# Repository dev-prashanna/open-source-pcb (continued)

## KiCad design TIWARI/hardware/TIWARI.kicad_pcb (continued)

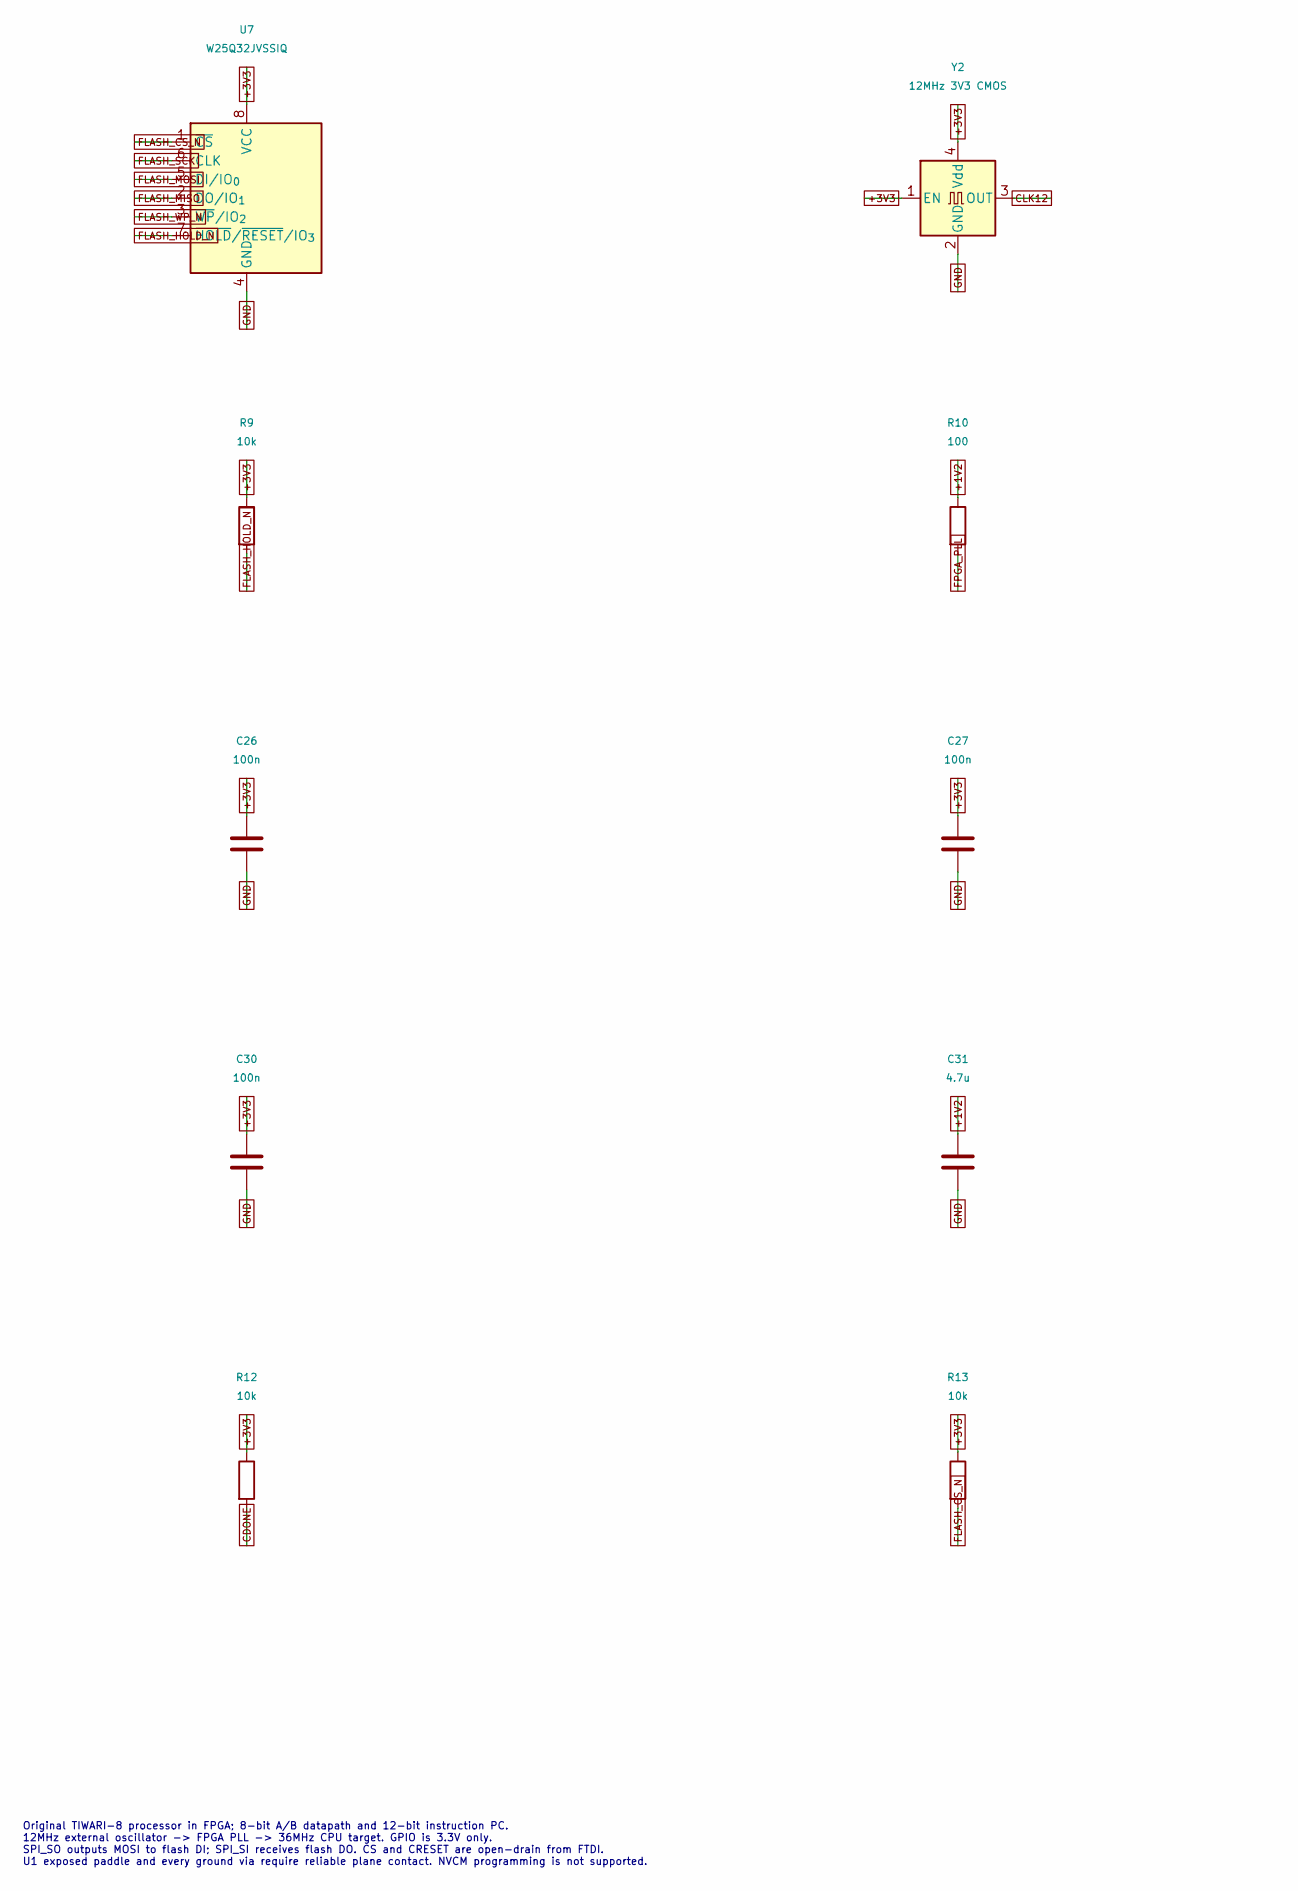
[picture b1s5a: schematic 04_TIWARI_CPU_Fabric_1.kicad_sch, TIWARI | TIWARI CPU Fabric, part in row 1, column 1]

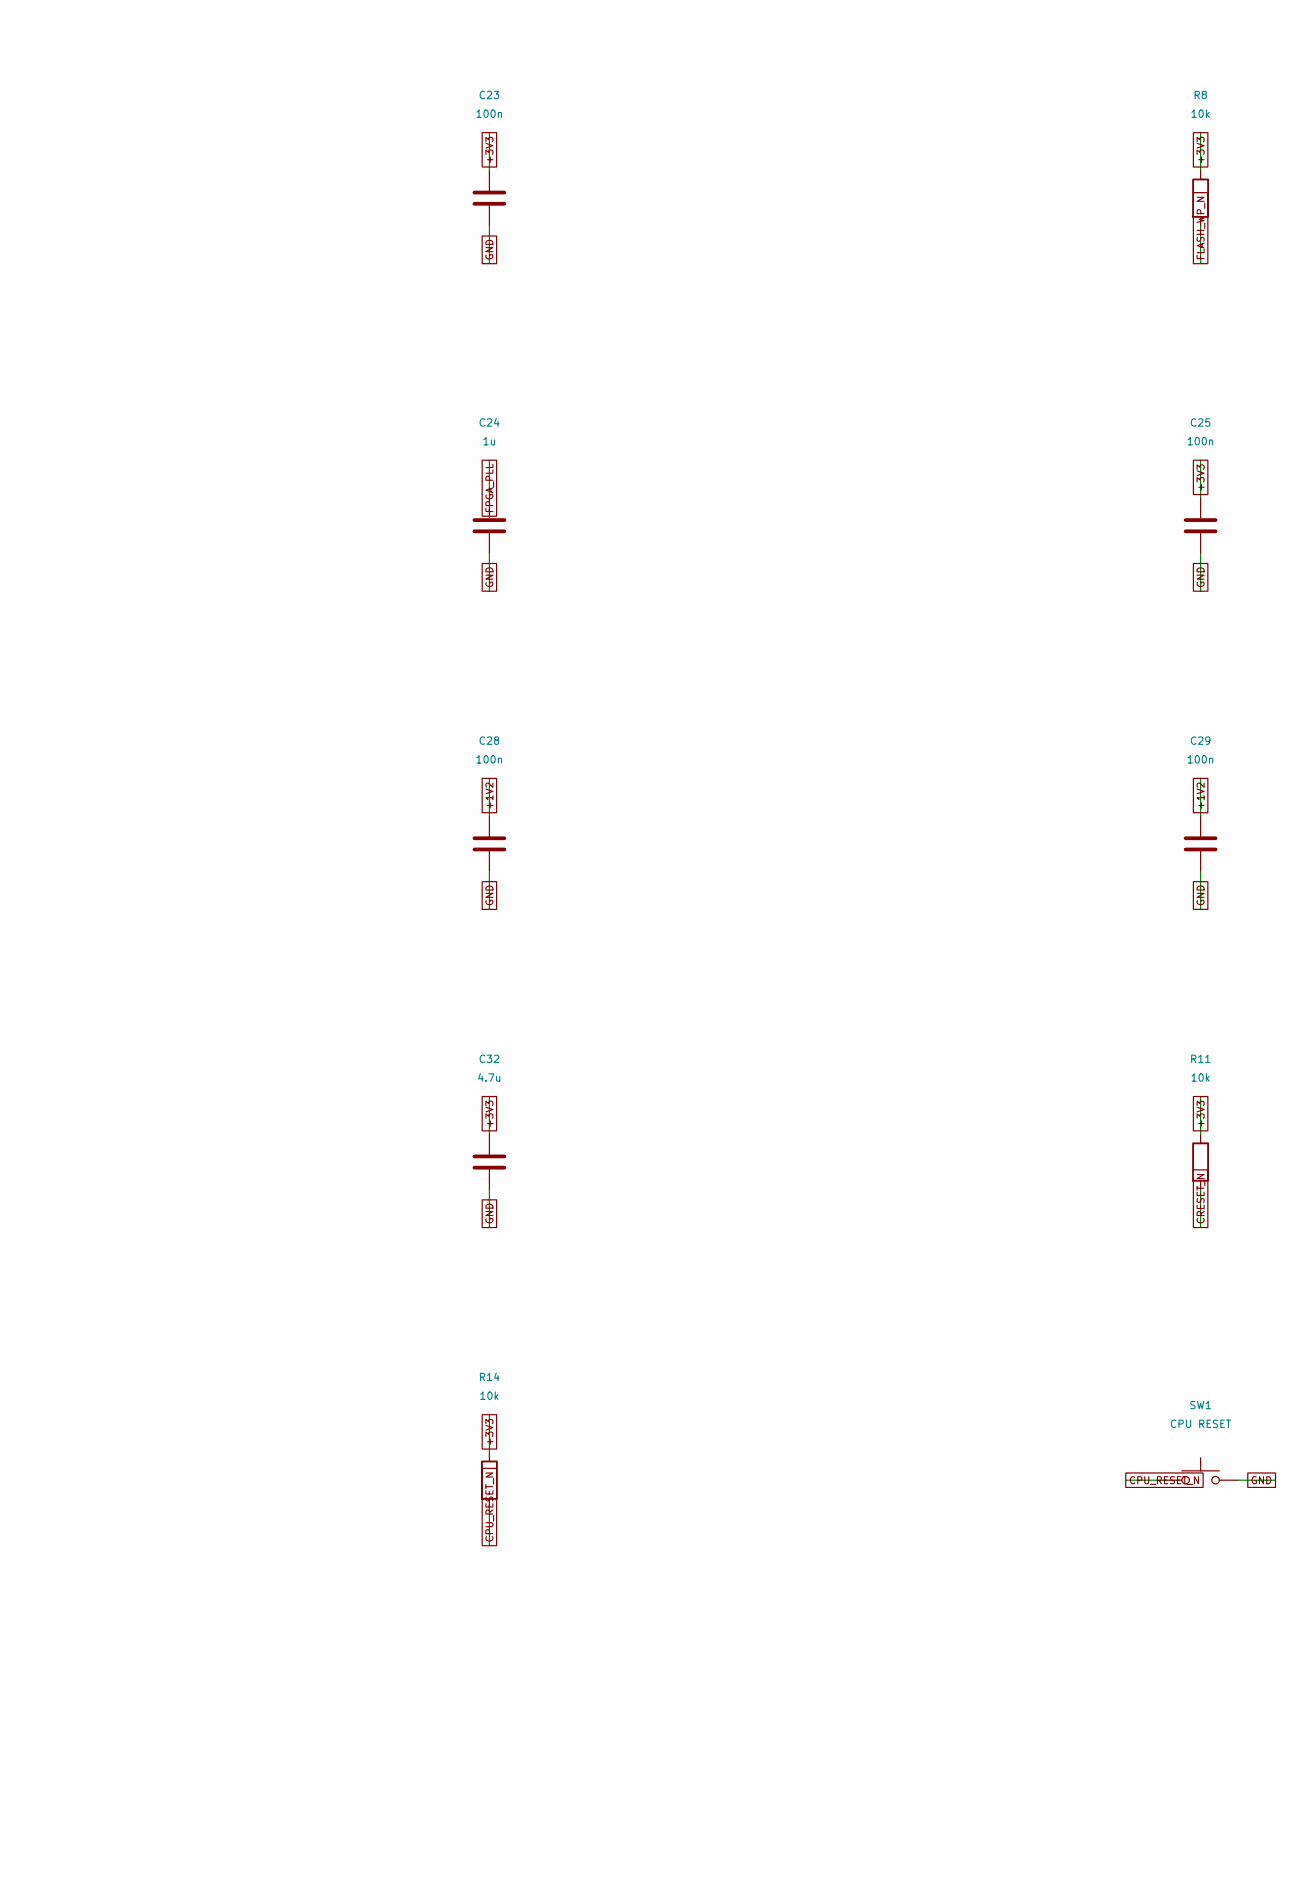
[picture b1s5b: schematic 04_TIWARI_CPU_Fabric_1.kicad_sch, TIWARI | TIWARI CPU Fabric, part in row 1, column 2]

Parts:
C23, C25, C26, C27, C28, C29, C30: 100n; C_0603_1608Metric; MPN GRM188R71C104KA01D
C24: 1u; C_0603_1608Metric; MPN GRM188R61A105KA61D
C31, C32: 4.7u; C_0805_2012Metric; MPN GRM21BR61A475KA73L
R8, R9, R11, R12, R13, R14: 10k; R_0603_1608Metric; MPN RC0603FR-0710KL
R10: 100; R_0603_1608Metric; MPN RC0603FR-07100RL
SW1: CPU RESET; SW_Push_1P1T-SH_NO_CK_KMR2xxG; MPN KMR221GLFS
U7: W25Q32JVSSIQ; SOIC-8_5.3x5.3mm_P1.27mm; MPN W25Q32JVSSIQ
Y2: 12MHz 3V3 CMOS; Oscillator_SMD_Abracon_ASE-4Pin_3.2x2.5mm; MPN ASE-12.000MHZ-LC-T

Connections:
+1V2: C28.1, C29.1, C31.1, R10.1; also elsewhere on the board
+3V3: C23.1, C25.1, C26.1, C27.1, C30.1, C32.1, R8.1, R9.1, R11.1, R12.1, R13.1, R14.1, U7.8 (VCC), Y2.1 (EN), Y2.4 (Vdd); also elsewhere on the board
CDONE: R12.2; also elsewhere on the board
CLK12: Y2.3 (OUT); also elsewhere on the board
CPU_RESET_N: R14.2, SW1.1; also elsewhere on the board
CRESET_N: R11.2; also elsewhere on the board
FLASH_CS_N: R13.2, U7.1 (~CS); also elsewhere on the board
FLASH_HOLD_N: R9.2, U7.7 (~HOLD/~RESET/IO_{3})
FLASH_MISO: U7.2 (DO/IO_{1}); also elsewhere on the board
FLASH_MOSI: U7.5 (DI/IO_{0}); also elsewhere on the board
FLASH_SCK: U7.6 (CLK); also elsewhere on the board
FLASH_WP_N: R8.2, U7.3 (~WP/IO_{2})
FPGA_PLL: C24.1, R10.2; also elsewhere on the board
GND: C23.2, C24.2, C25.2, C26.2, C27.2, C28.2, C29.2, C30.2, C31.2, C32.2, SW1.2, U7.4 (GND), Y2.2 (GND); also elsewhere on the board

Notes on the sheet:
Original TIWARI-8 processor in FPGA; 8-bit A/B datapath and 12-bit instruction PC. 12MHz external oscillator -> FPGA PLL -> 36MHz CPU target. GPIO is 3.3V only. SPI_SO outputs MOSI to flash DI; SPI_SI receives flash DO. CS and CRESET are open-drain from FTDI. U1 exposed paddle and every ground via 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

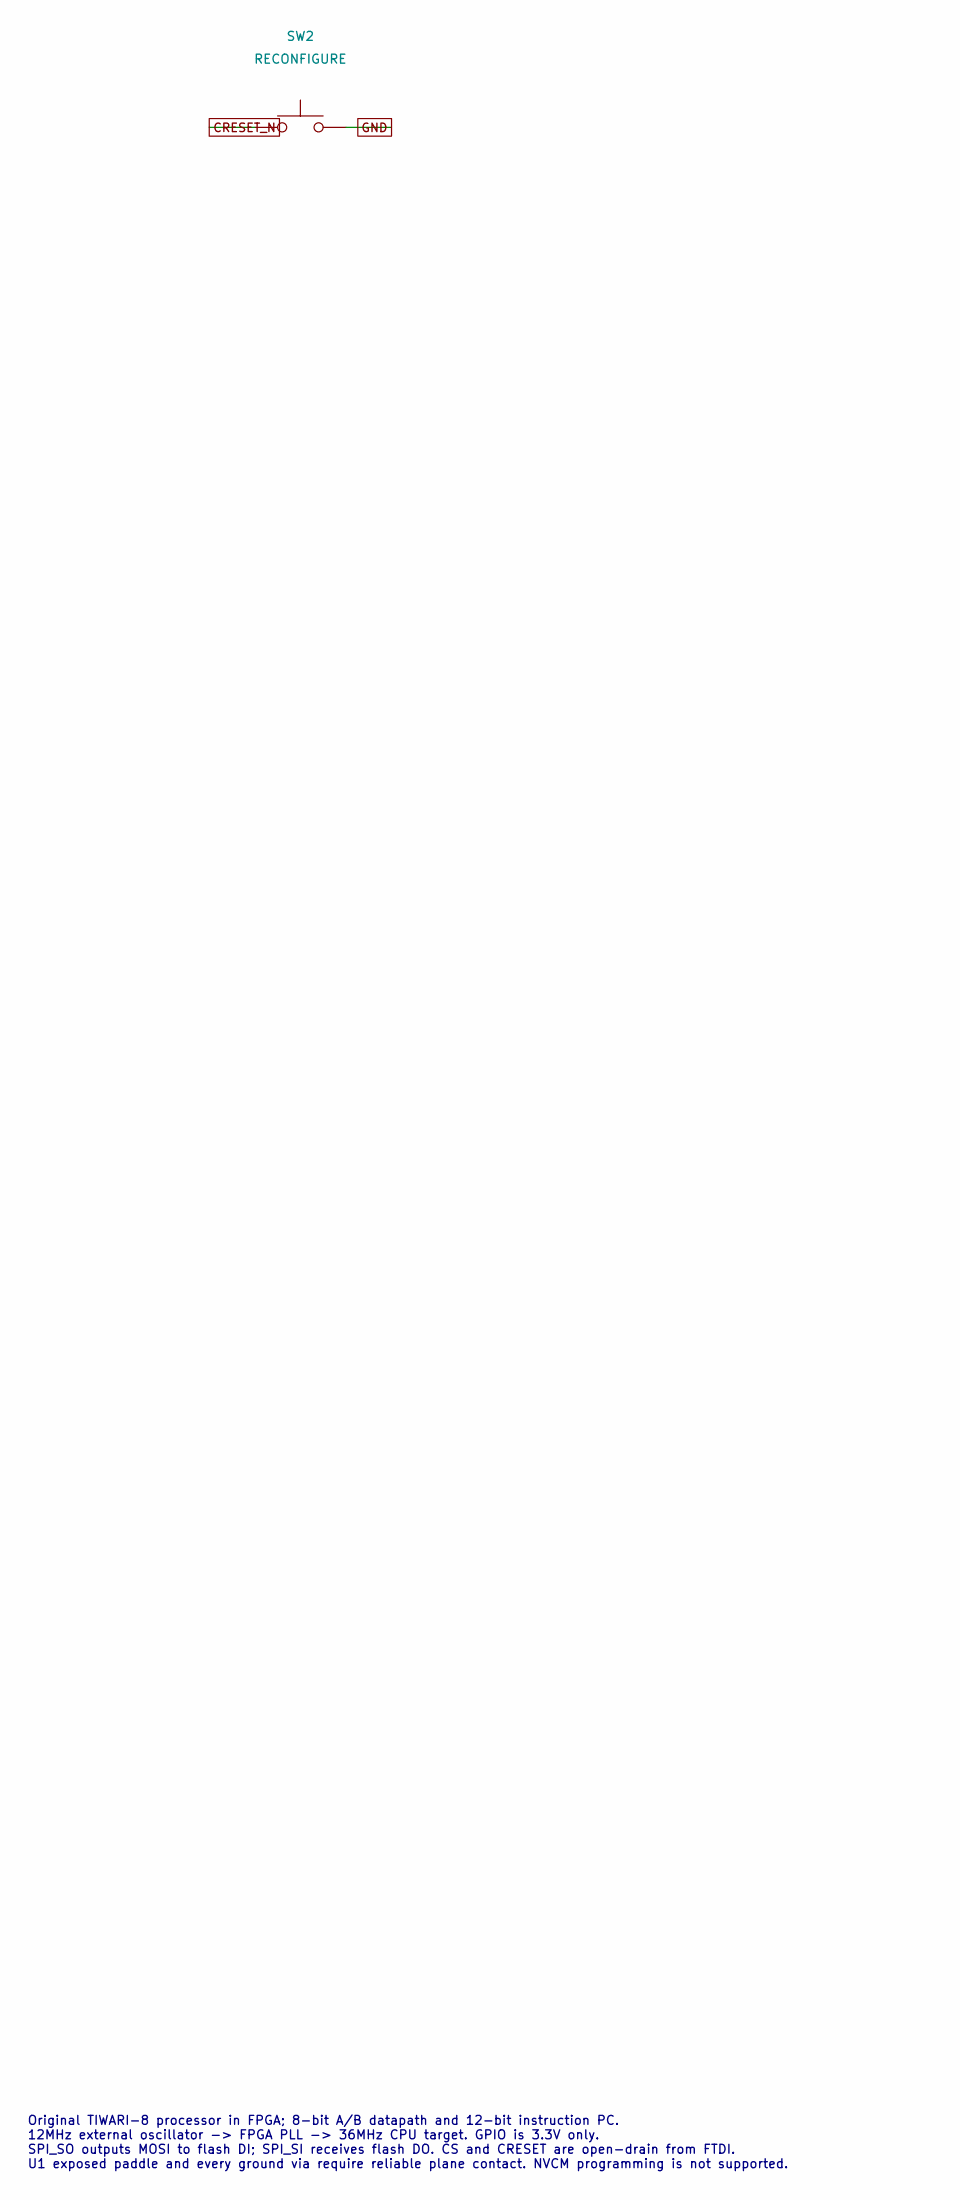
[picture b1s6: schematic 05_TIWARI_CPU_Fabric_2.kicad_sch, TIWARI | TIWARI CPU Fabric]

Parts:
SW2: RECONFIGURE; SW_Push_1P1T-SH_NO_CK_KMR2xxG; MPN KMR221GLFS

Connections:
CRESET_N: SW2.1; also elsewhere on the board
GND: SW2.2; also elsewhere on the board

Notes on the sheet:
Original TIWARI-8 processor in FPGA; 8-bit A/B datapath and 12-bit instruction PC. 12MHz external oscillator -> FPGA PLL -> 36MHz CPU target. GPIO is 3.3V only. SPI_SO outputs MOSI to flash DI; SPI_SI receives flash DO. CS and CRESET are open-drain from FTDI. U1 exposed paddle and every ground via 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

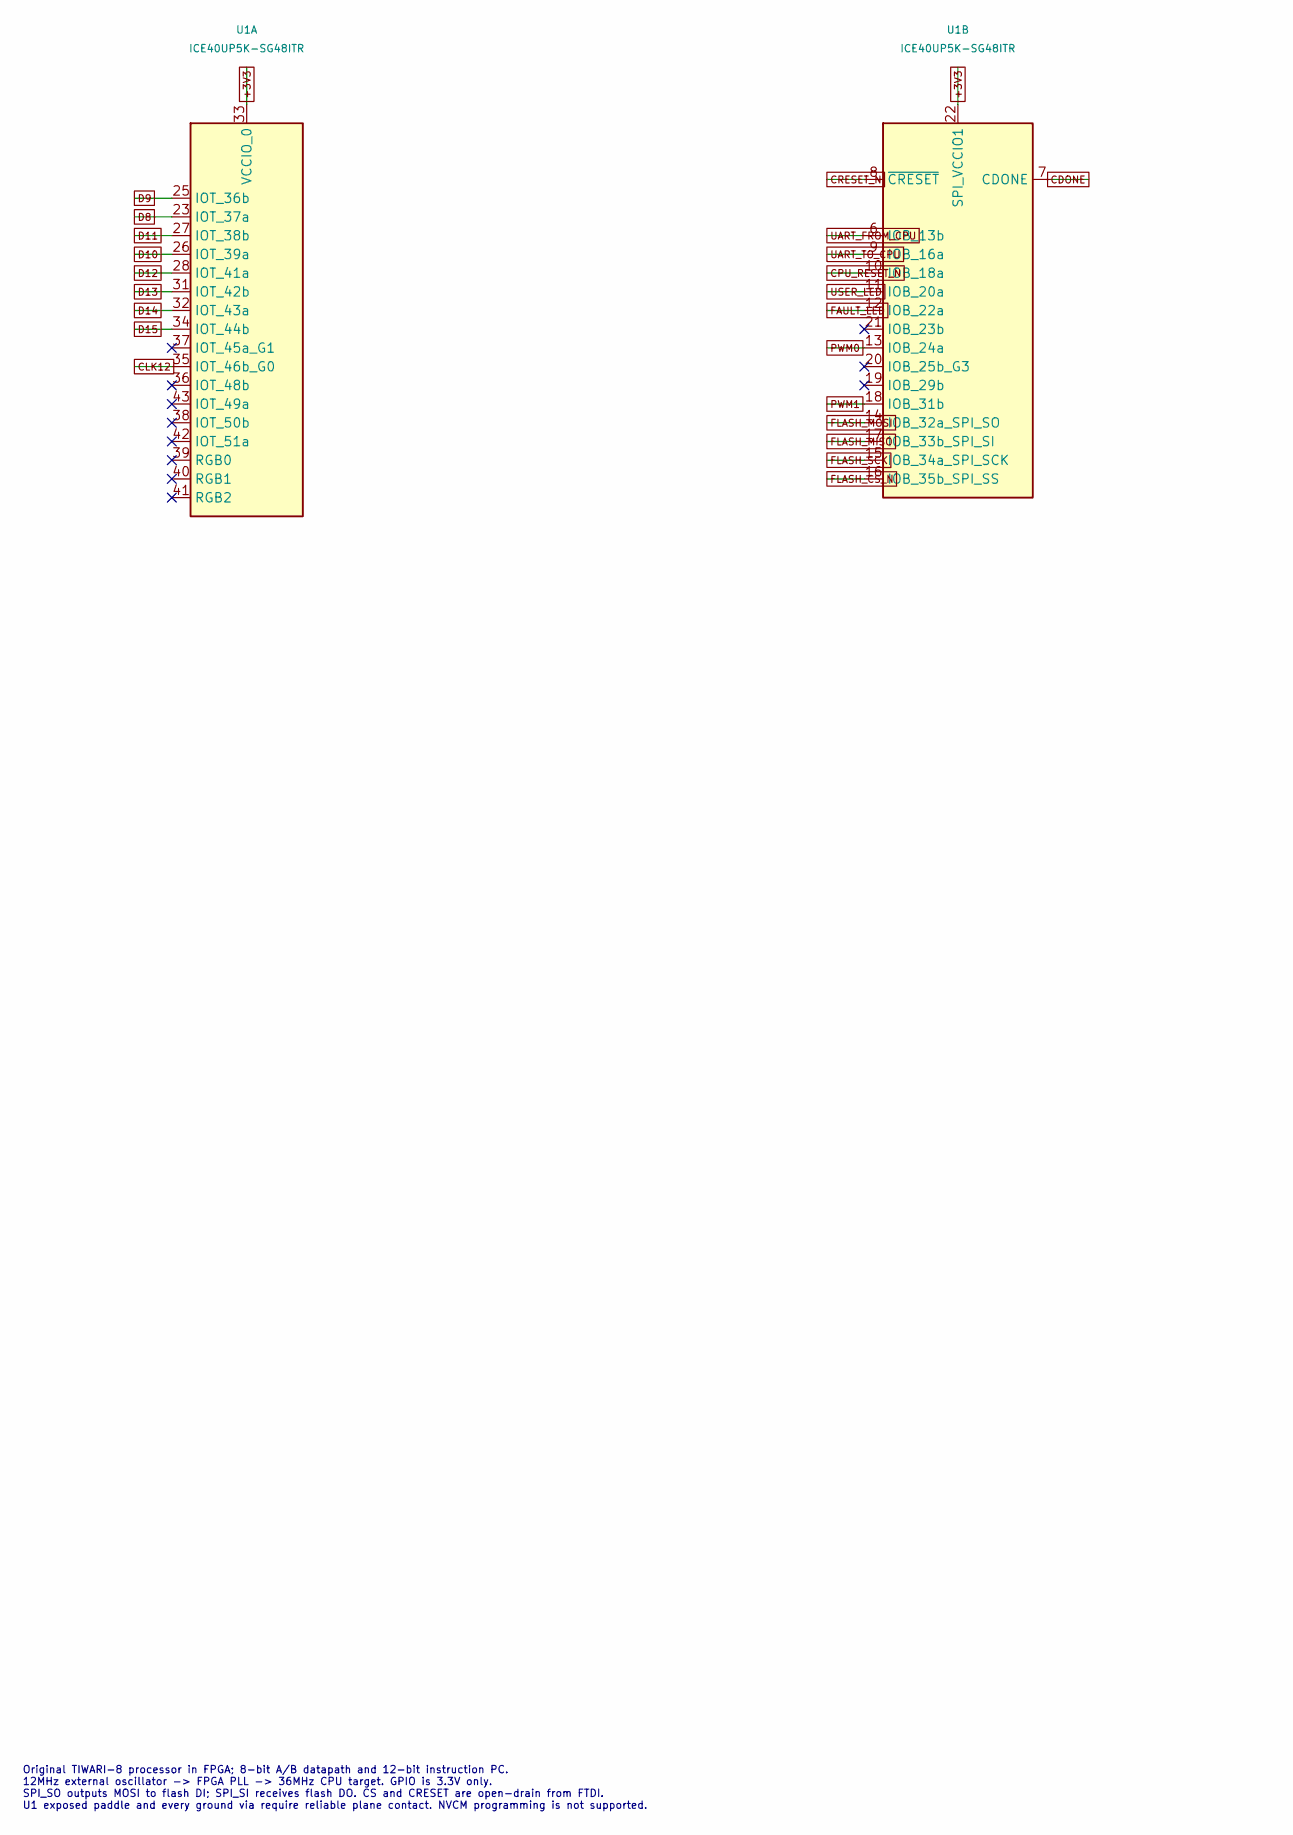
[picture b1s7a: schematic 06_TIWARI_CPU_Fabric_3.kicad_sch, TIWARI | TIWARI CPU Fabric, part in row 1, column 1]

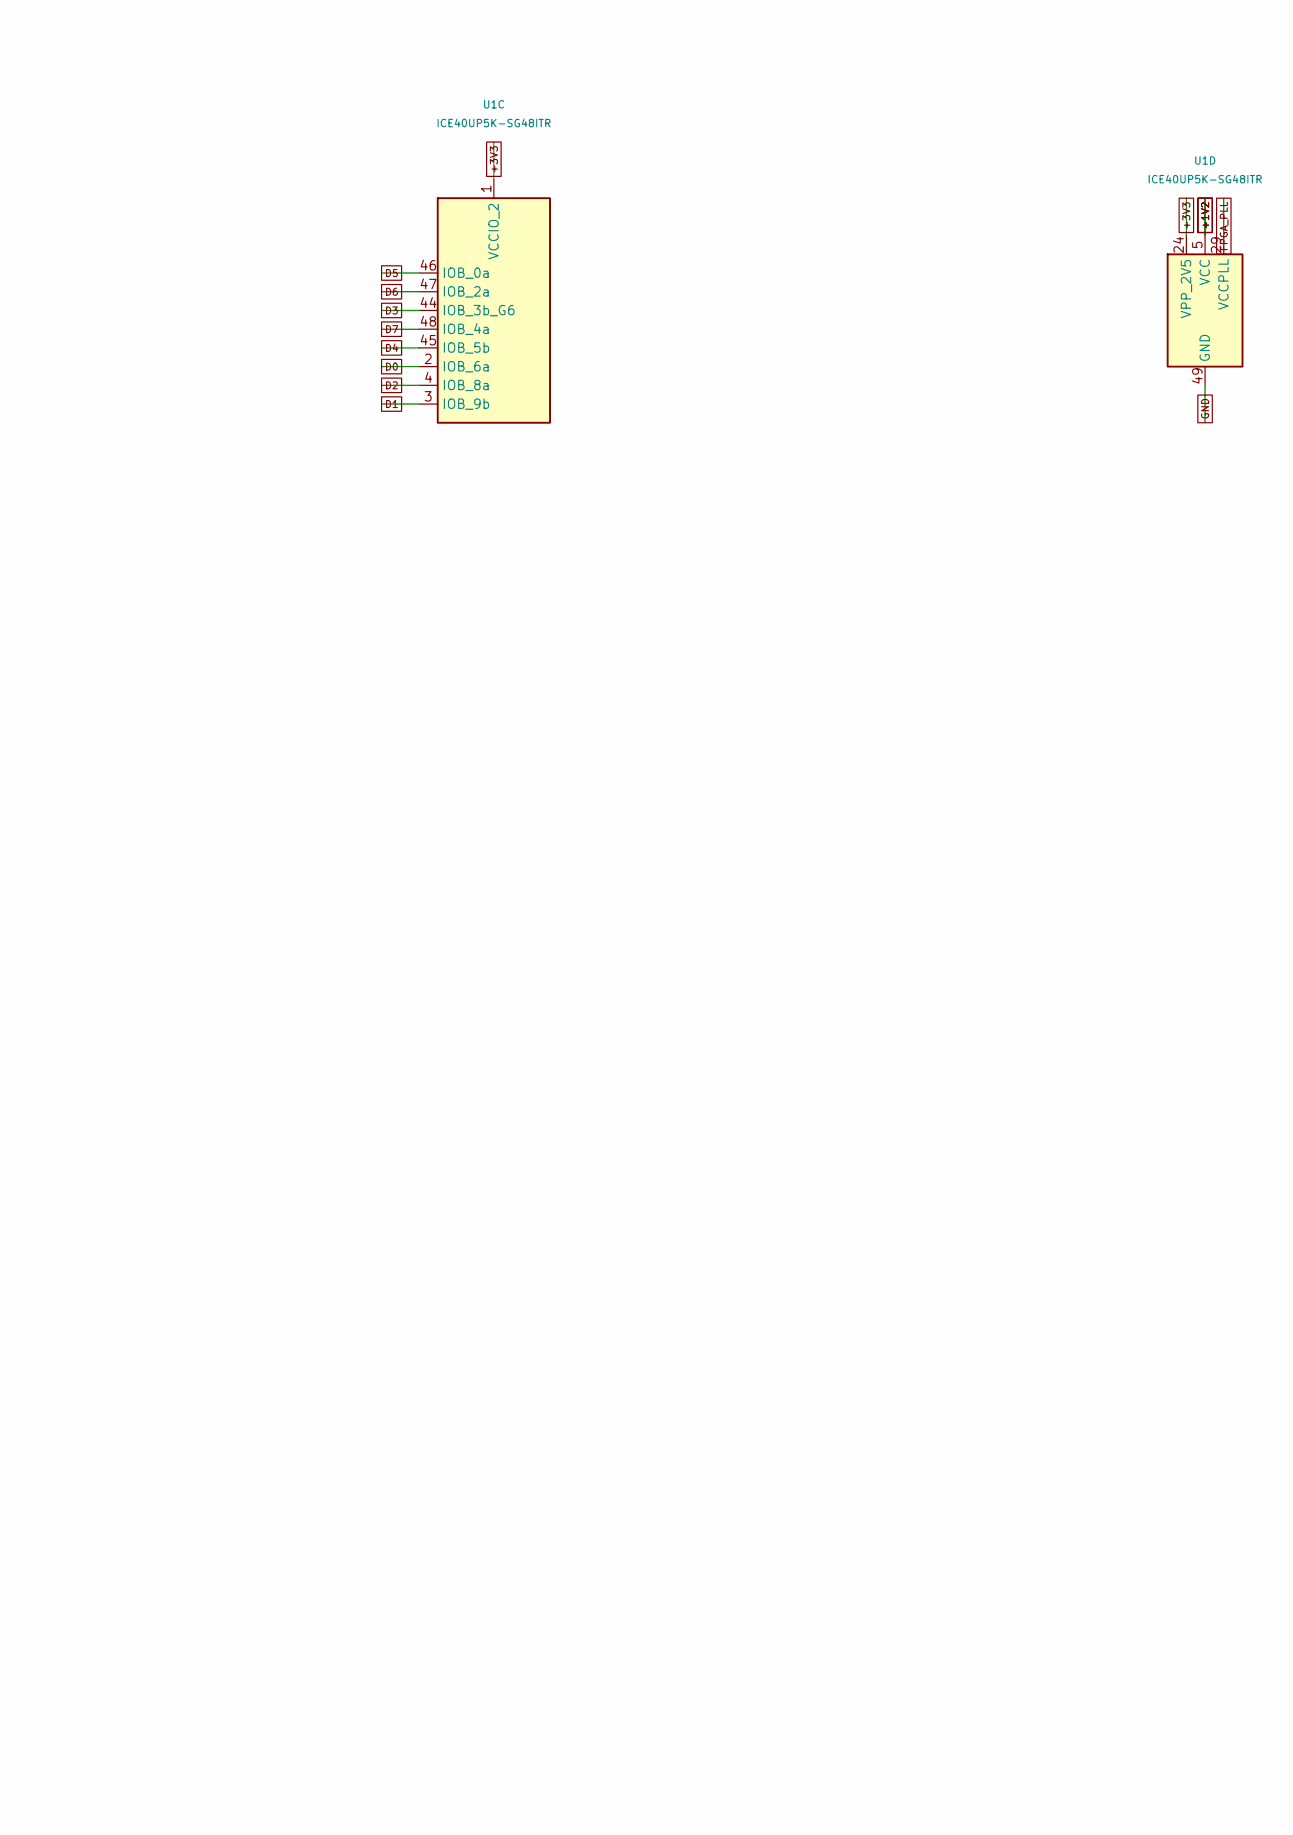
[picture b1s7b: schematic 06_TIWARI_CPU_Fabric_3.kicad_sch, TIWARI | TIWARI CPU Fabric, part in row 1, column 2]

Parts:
U1: ICE40UP5K-SG48ITR; UP5K_SG48_Reviewed; MPN ICE40UP5K-SG48ITR

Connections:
+1V2: U1.5 (VCC), U1.30 (VCC); also elsewhere on the board
+3V3: U1.1 (VCCIO_2), U1.22 (SPI_VCCIO1), U1.24 (VPP_2V5), U1.33 (VCCIO_0); also elsewhere on the board
CDONE: U1.7 (CDONE); also elsewhere on the board
CLK12: U1.35 (IOT_46b_G0); also elsewhere on the board
CPU_RESET_N: U1.10 (IOB_18a); also elsewhere on the board
CRESET_N: U1.8 (~CRESET); also elsewhere on the board
D0: U1.2 (IOB_6a); also elsewhere on the board
D1: U1.3 (IOB_9b); also elsewhere on the board
D2: U1.4 (IOB_8a); also elsewhere on the board
D3: U1.44 (IOB_3b_G6); also elsewhere on the board
D4: U1.45 (IOB_5b); also elsewhere on the board
D5: U1.46 (IOB_0a); also elsewhere on the board
D6: U1.47 (IOB_2a); also elsewhere on the board
D7: U1.48 (IOB_4a); also elsewhere on the board
D8: U1.23 (IOT_37a); also elsewhere on the board
D9: U1.25 (IOT_36b); also elsewhere on the board
D10: U1.26 (IOT_39a); also elsewhere on the board
D11: U1.27 (IOT_38b); also elsewhere on the board
D12: U1.28 (IOT_41a); also elsewhere on the board
D13: U1.31 (IOT_42b); also elsewhere on the board
D14: U1.32 (IOT_43a); also elsewhere on the board
D15: U1.34 (IOT_44b); also elsewhere on the board
FAULT_LED: U1.12 (IOB_22a); also elsewhere on the board
FLASH_CS_N: U1.16 (IOB_35b_SPI_SS); also elsewhere on the board
FLASH_MISO: U1.17 (IOB_33b_SPI_SI); also elsewhere on the board
FLASH_MOSI: U1.14 (IOB_32a_SPI_SO); also elsewhere on the board
FLASH_SCK: U1.15 (IOB_34a_SPI_SCK); also elsewhere on the board
FPGA_PLL: U1.29 (VCCPLL); also elsewhere on the board
GND: U1.49 (GND); also elsewhere on the board
PWM0: U1.13 (IOB_24a); also elsewhere on the board
PWM1: U1.18 (IOB_31b); also elsewhere on the board
UART_FROM_CPU: U1.6 (IOB_13b); also elsewhere on the board
UART_TO_CPU: U1.9 (IOB_16a); also elsewhere on the board
USER_LED: U1.11 (IOB_20a); also elsewhere on the board

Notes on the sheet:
Original TIWARI-8 processor in FPGA; 8-bit A/B datapath and 12-bit instruction PC. 12MHz external oscillator -> FPGA PLL -> 36MHz CPU target. GPIO is 3.3V only. SPI_SO outputs MOSI to flash DI; SPI_SI receives flash DO. CS and CRESET are open-drain from FTDI. U1 exposed paddle and every ground via 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

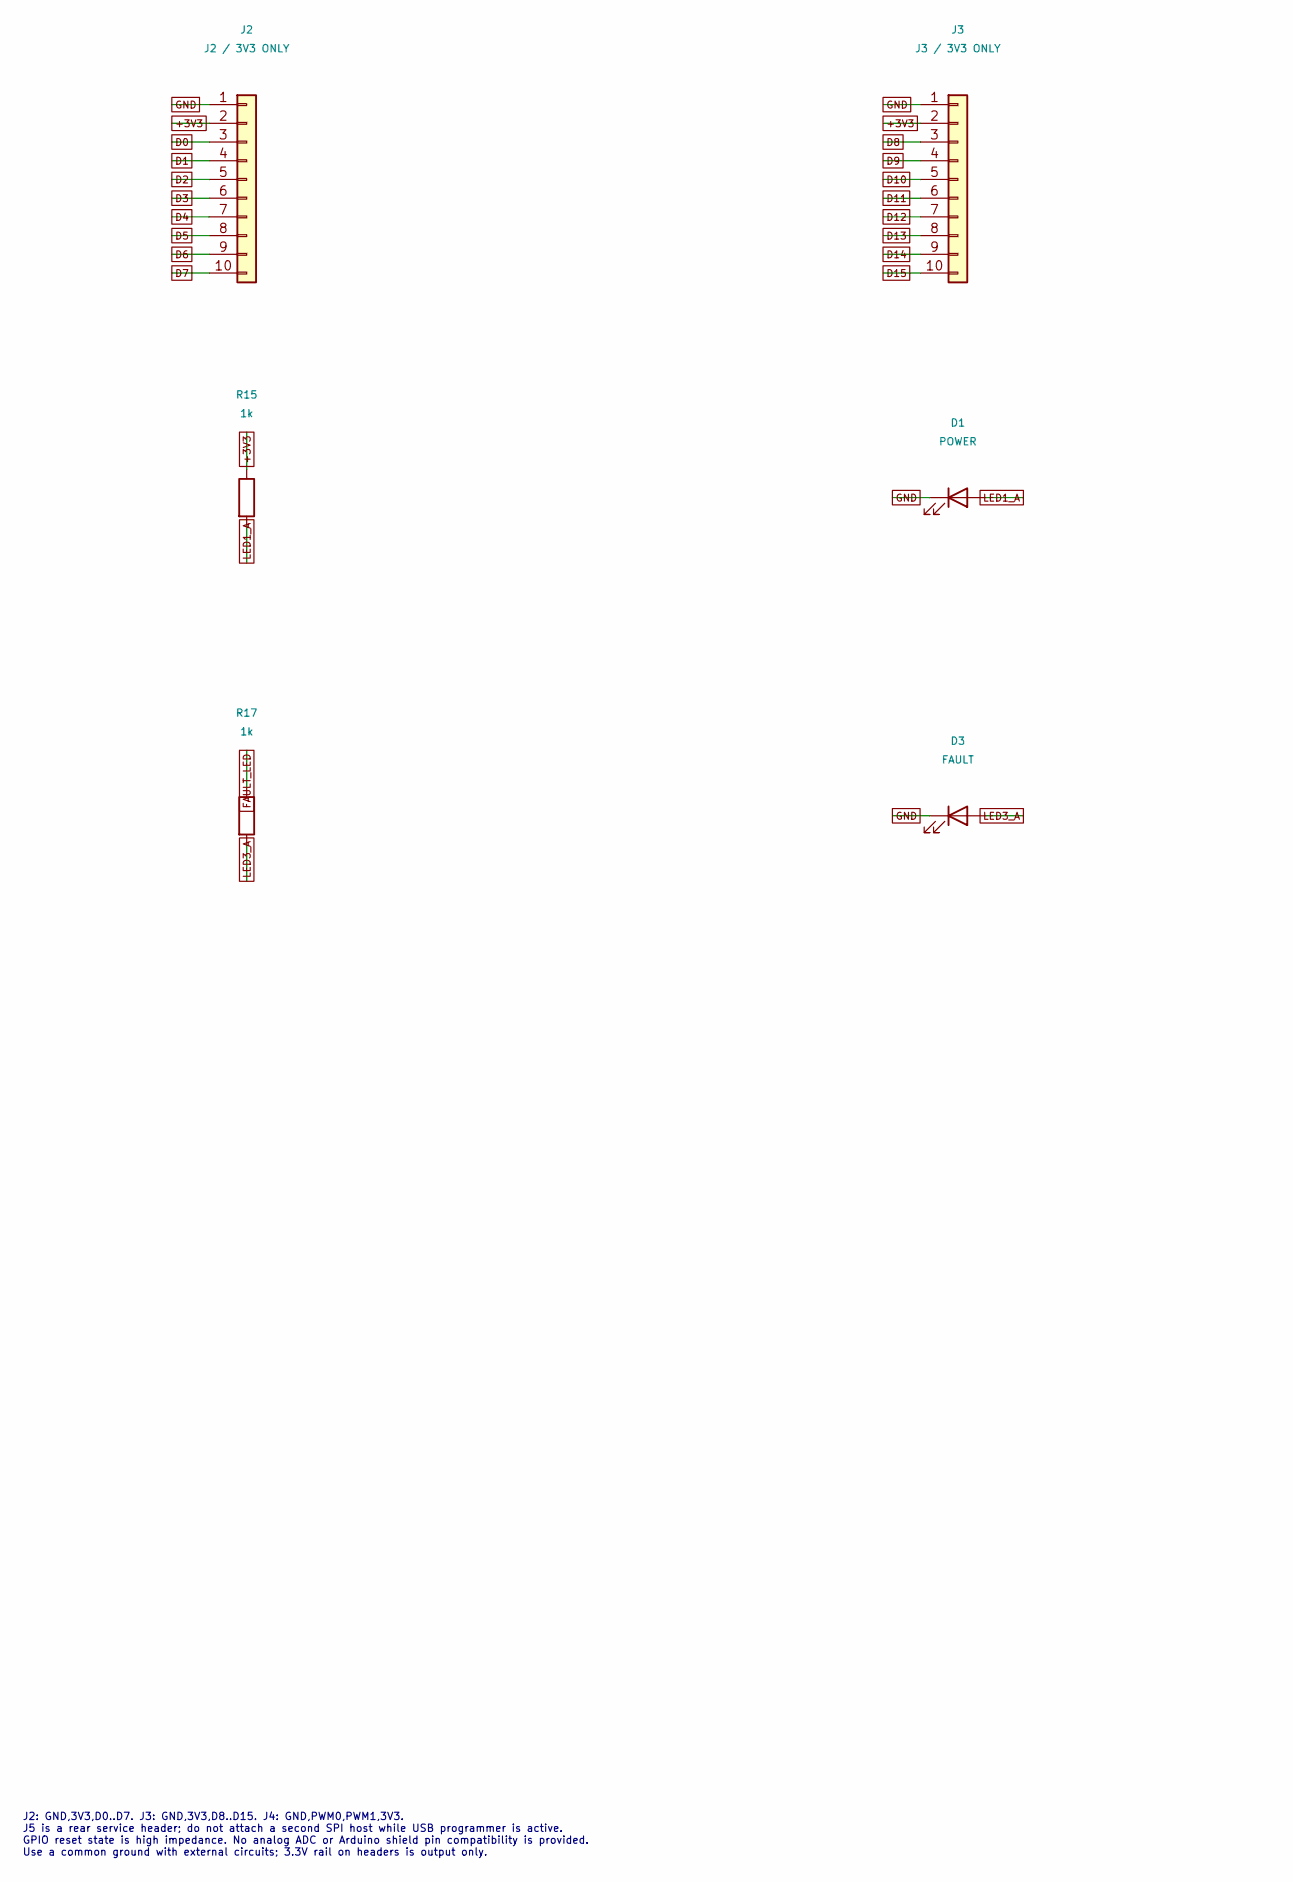
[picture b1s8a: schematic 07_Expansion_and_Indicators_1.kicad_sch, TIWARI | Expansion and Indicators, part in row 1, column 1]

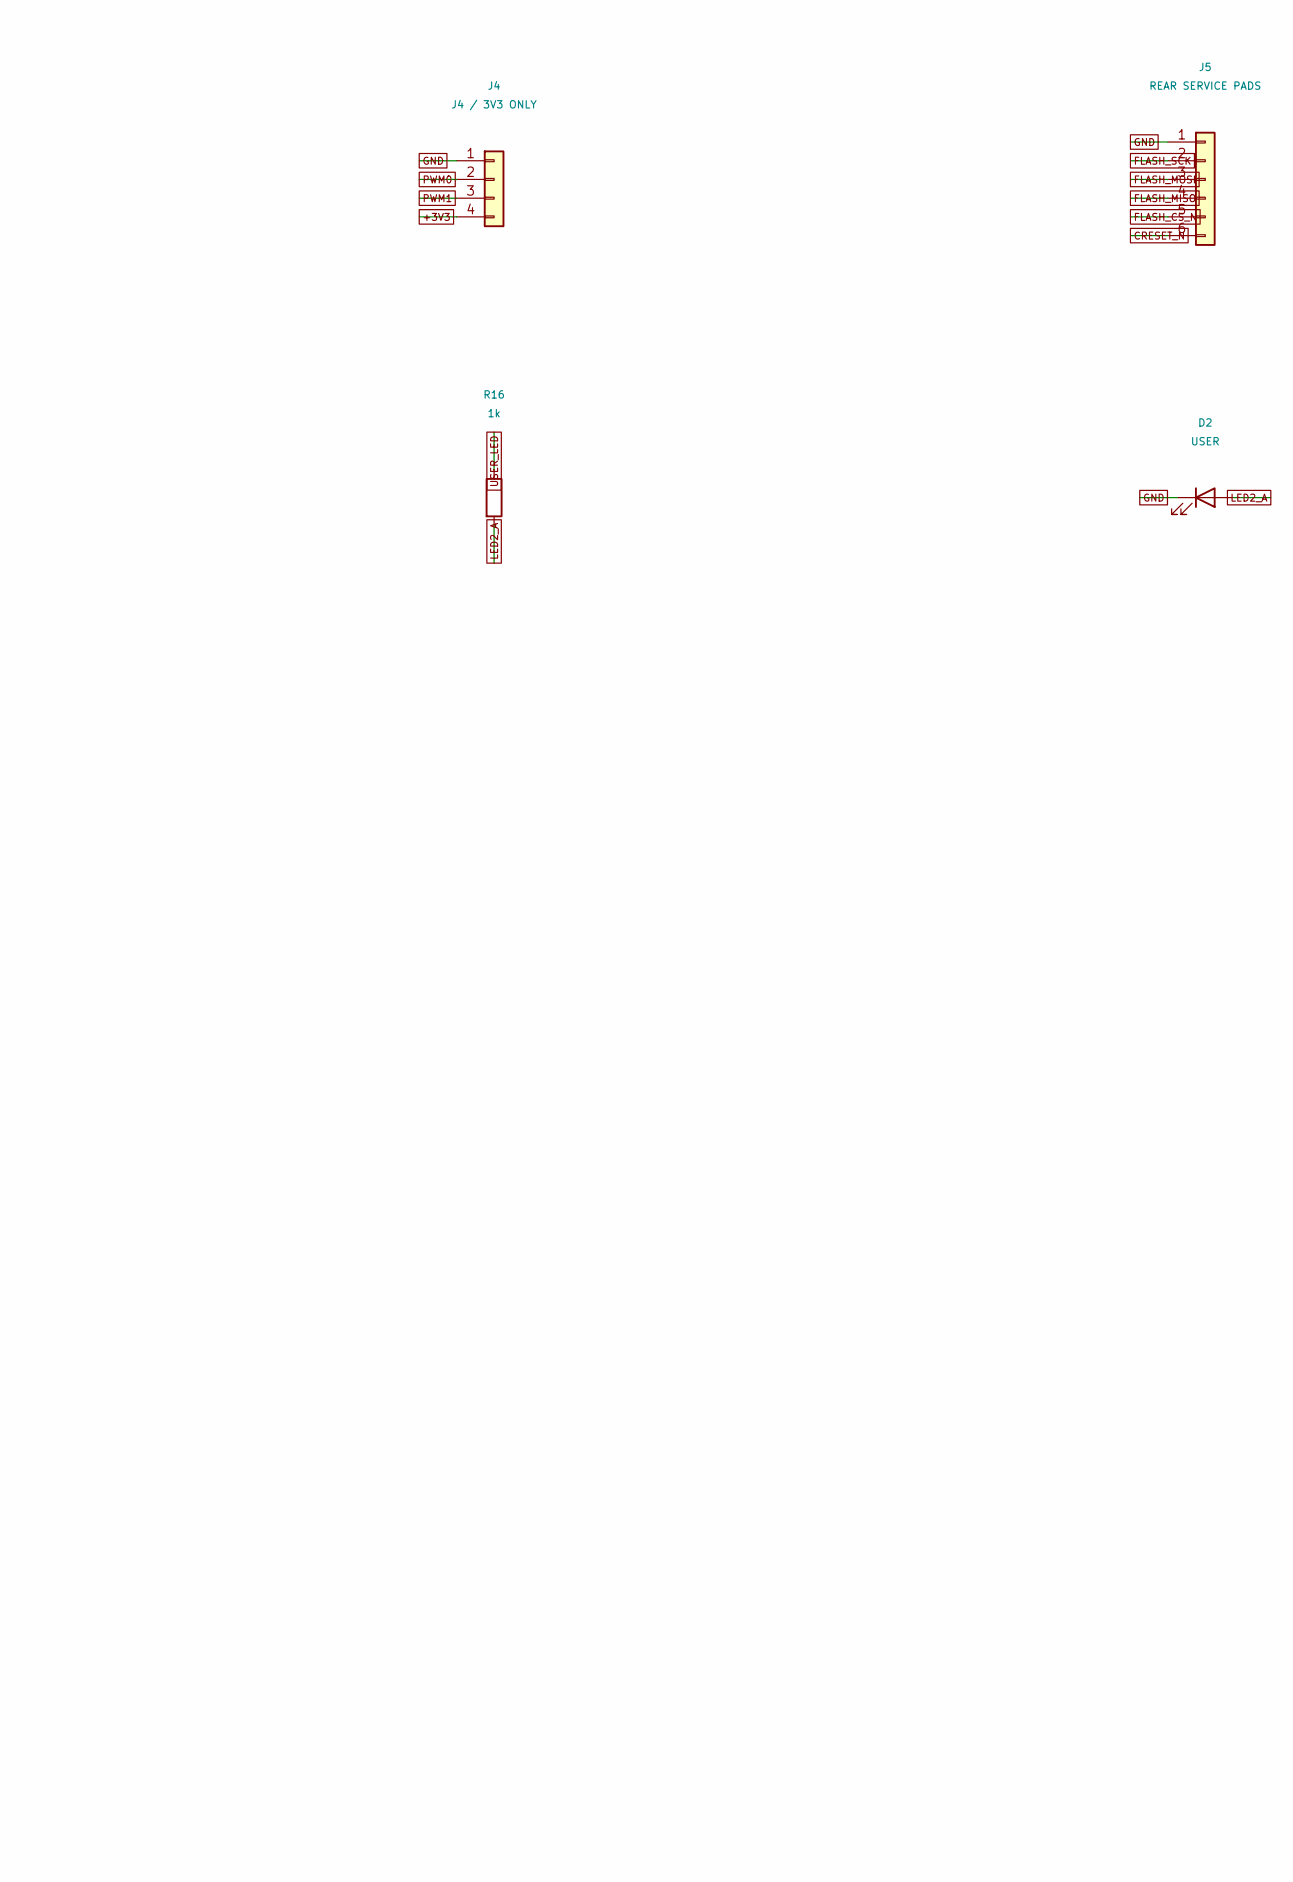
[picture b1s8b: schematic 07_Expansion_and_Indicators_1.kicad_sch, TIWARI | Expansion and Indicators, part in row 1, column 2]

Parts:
D1: POWER; LED_0603_1608Metric; MPN LTST-C190KGKT
D2: USER; LED_0603_1608Metric; MPN LTST-C190KGKT
D3: FAULT; LED_0603_1608Metric; MPN LTST-C190KRKT
J2: J2 / 3V3 ONLY; PinHeader_1x10_P2.54mm_Vertical; MPN 61301011121
J3: J3 / 3V3 ONLY; PinHeader_1x10_P2.54mm_Vertical; MPN 61301011121
J4: J4 / 3V3 ONLY; PinHeader_1x04_P2.54mm_Vertical; MPN 61300411121
J5: REAR SERVICE PADS; ServicePads_1x06_P1.27; MPN PCB_FEATURE
R15, R16, R17: 1k; R_0603_1608Metric; MPN RC0603FR-071KL

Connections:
+3V3: J2.2, J3.2, J4.4, R15.1; also elsewhere on the board
CRESET_N: J5.6; also elsewhere on the board
D0: J2.3; also elsewhere on the board
D1: J2.4; also elsewhere on the board
D2: J2.5; also elsewhere on the board
D3: J2.6; also elsewhere on the board
D4: J2.7; also elsewhere on the board
D5: J2.8; also elsewhere on the board
D6: J2.9; also elsewhere on the board
D7: J2.10; also elsewhere on the board
D8: J3.3; also elsewhere on the board
D9: J3.4; also elsewhere on the board
D10: J3.5; also elsewhere on the board
D11: J3.6; also elsewhere on the board
D12: J3.7; also elsewhere on the board
D13: J3.8; also elsewhere on the board
D14: J3.9; also elsewhere on the board
D15: J3.10; also elsewhere on the board
FAULT_LED: R17.1; also elsewhere on the board
FLASH_CS_N: J5.5; also elsewhere on the board
FLASH_MISO: J5.4; also elsewhere on the board
FLASH_MOSI: J5.3; also elsewhere on the board
FLASH_SCK: J5.2; also elsewhere on the board
GND: D1.1 (K), D2.1 (K), D3.1 (K), J2.1, J3.1, J4.1, J5.1; also elsewhere on the board
LED1_A: D1.2 (A), R15.2
LED2_A: D2.2 (A), R16.2
LED3_A: D3.2 (A), R17.2
PWM0: J4.2; also elsewhere on the board
PWM1: J4.3; also elsewhere on the board
USER_LED: R16.1; also elsewhere on the board

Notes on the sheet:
J2: GND,3V3,D0..D7. J3: GND,3V3,D8..D15. J4: GND,PWM0,PWM1,3V3. J5 is a rear service header; do not attach a second SPI host while USB programmer is active. GPIO reset state is high impedance. No analog ADC or Arduino shield pin compatibility is provided. Use a common ground with external circuits;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
